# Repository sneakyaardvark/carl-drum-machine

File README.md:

# C.A.R.L. — Clocked Asynchronous Rhythm Logician

**Team 05:**  
Bao Nguyen  
Andrew Stanton  
Christian Mickelson  
Ethan Budde  

---

## Overview
C.A.R.L. is a portable drum sequencer that lets users tap out, save, and play rhythmic patterns. It operates independently with onboard controls, display, and speaker.

---

## Features
- Sequences and plays drum beats  
- Onboard speaker and volume control  
- Standalone operation (no computer required)  
- 13 pushbuttons, LED indicators, LCD display  
- Optional MIDI, SD card, and battery power  

---

## Hardware
- **Processor:** ESP32  
- **Display:** 20×4 LCD  
- **Inputs:** 13 pushbuttons, 4 potentiometers  
- **Outputs:** LEDs, speaker (8 Ω), LCD  
- **Power:** 5 V barrel jack or optional battery  
- **Enclosure:** Laser-cut plywood + 3D printed parts  

---

## Development
- **Electronics:** KiCAD  
- **3D Design:** Fusion 360  
- **Firmware:** Arduino / PlatformIO

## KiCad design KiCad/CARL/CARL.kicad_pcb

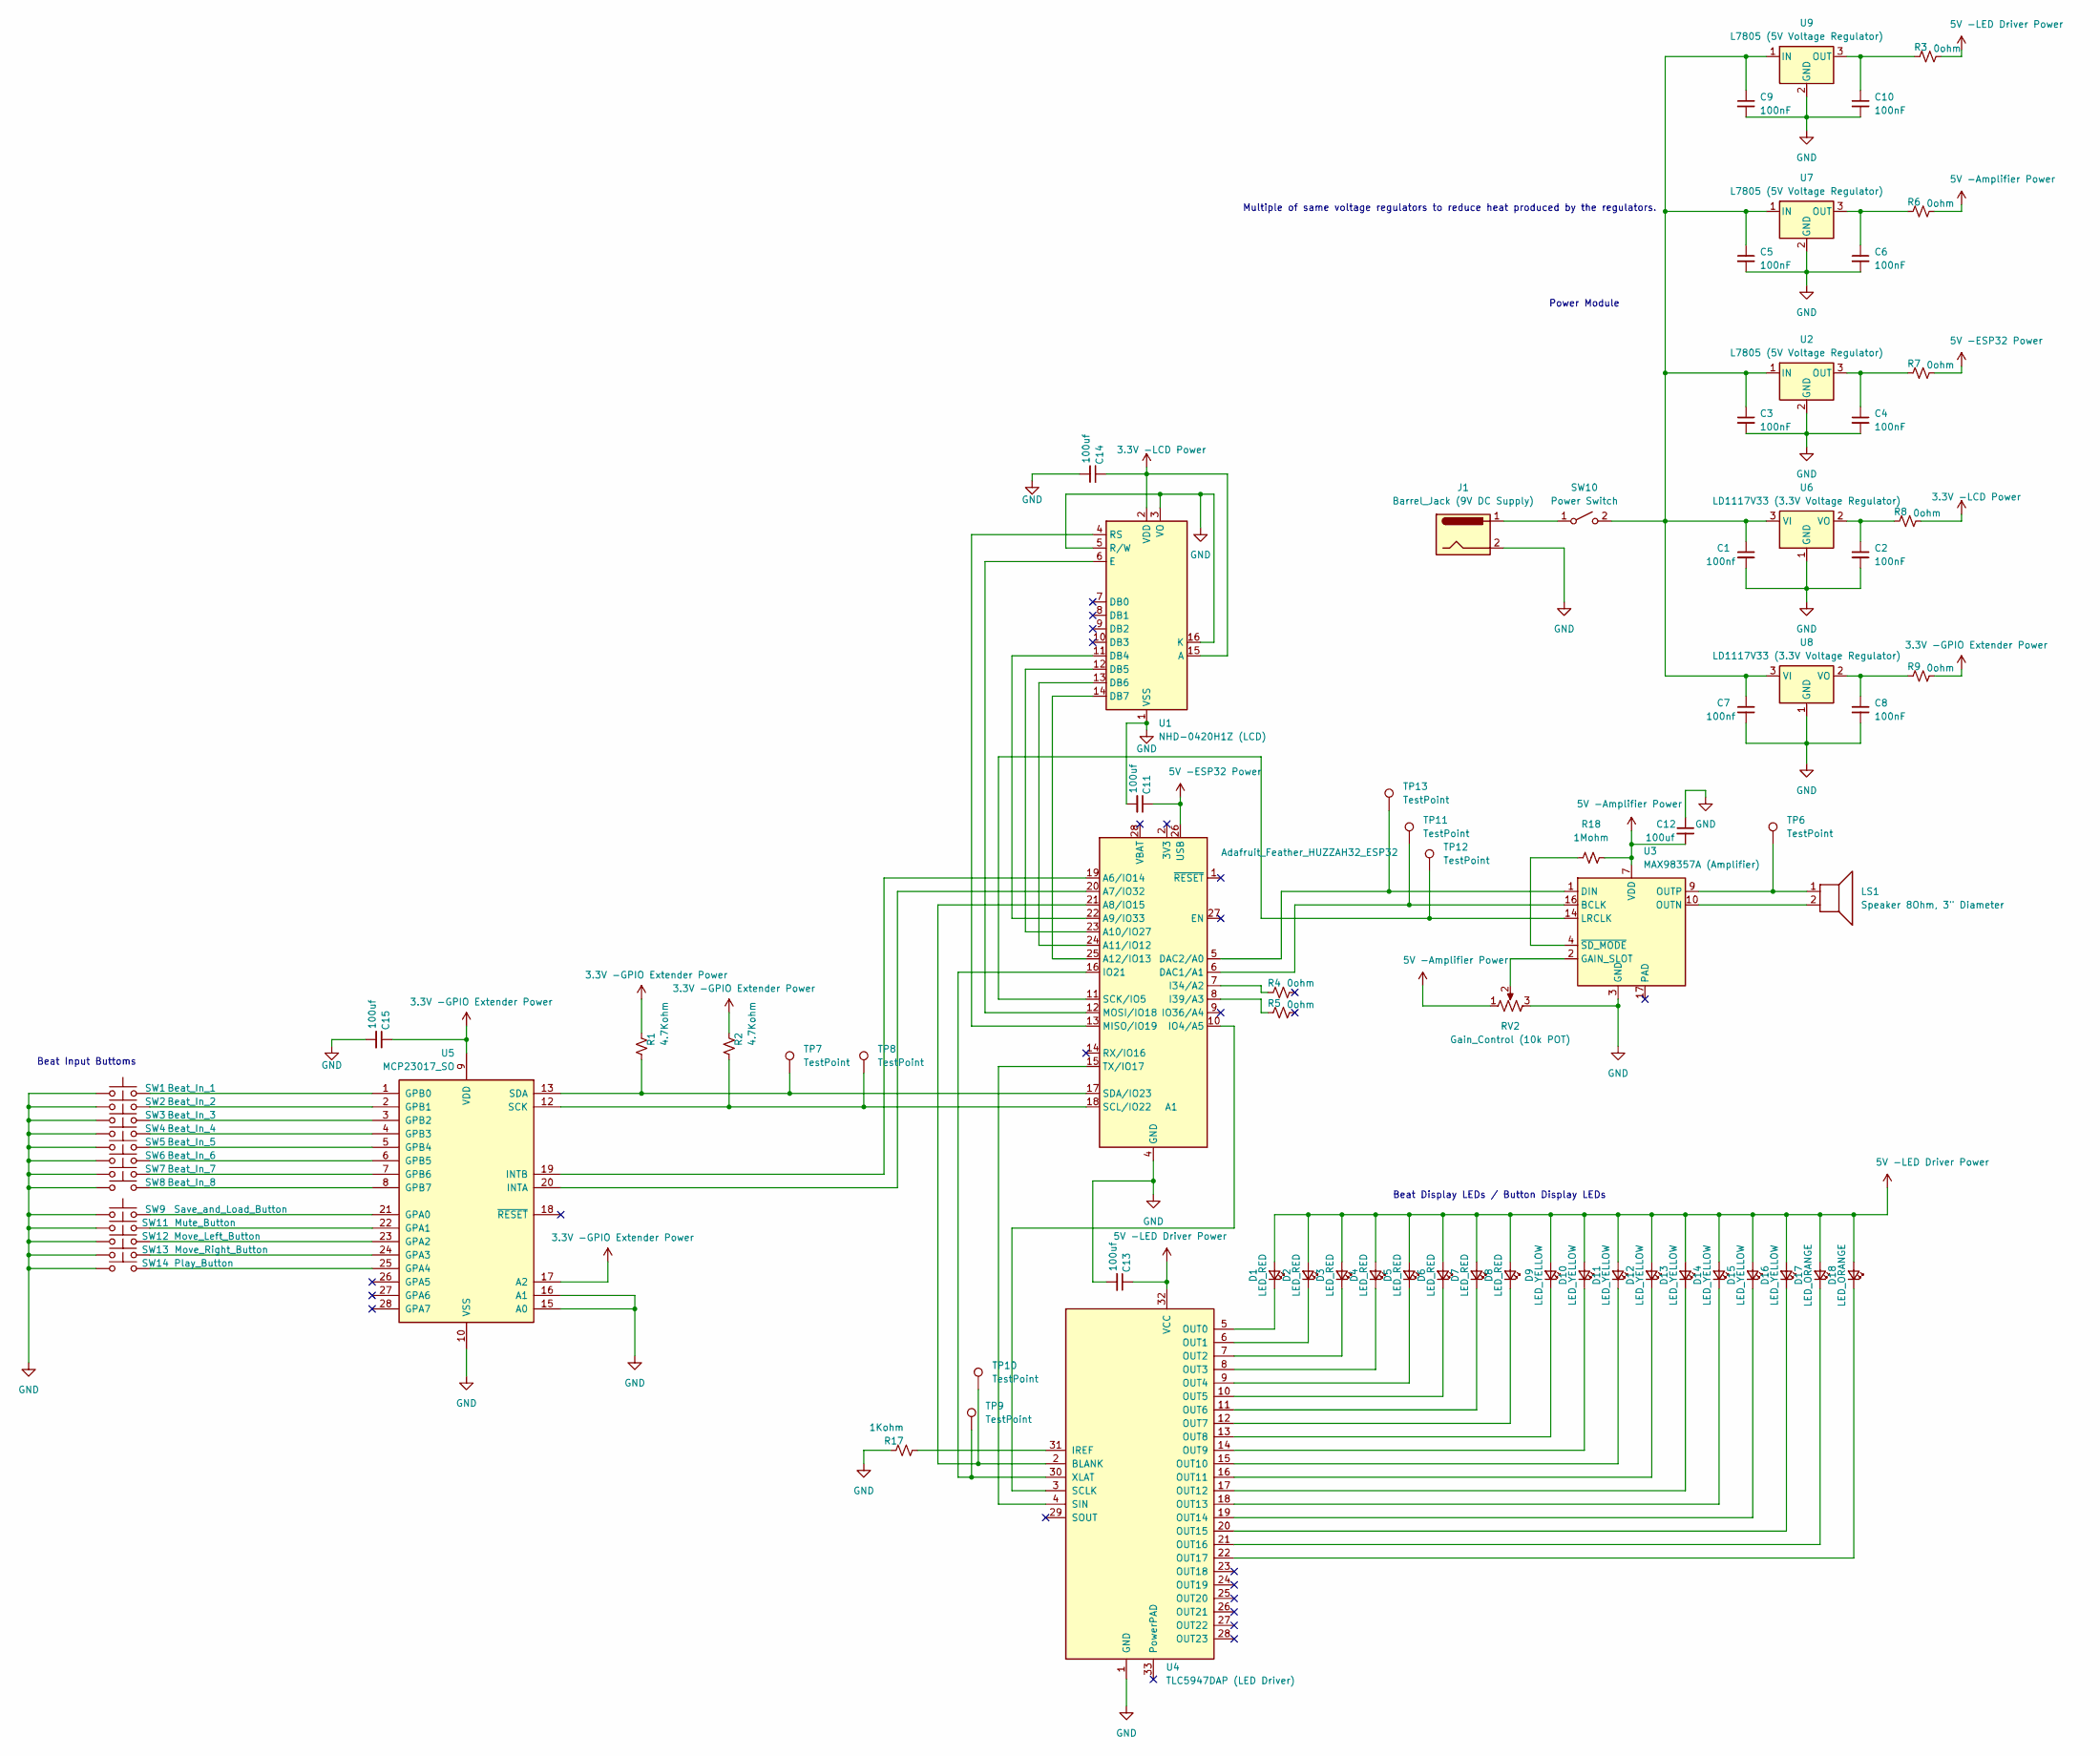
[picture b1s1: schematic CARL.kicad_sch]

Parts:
A1: Adafruit_Feather_HUZZAH32_ESP32; Adafruit_Feather
C1, C7: 100nf; C_0805_2012Metric
C2, C3, C4, C5, C6, C8, C9, C10: 100nF; C_0805_2012Metric
C11, C12, C13, C14, C15: 100uf; C_0805_2012Metric
D1, D2, D3, D4, D5, D6, D7, D8: LED_RED; LED_D5.0mm
D9, D10, D11, D12, D13, D14, D15, D16: LED_YELLOW; LED_D5.0mm
D17, D18: LED_ORANGE; LED_D5.0mm
J1: Barrel_Jack (9V DC Supply); BarrelJack_CUI_PJ-036AH-SMT_Horizontal
LS1: Speaker 8Ohm, 3" Diameter; Speaker_CUI_CMR-1206S-67
R1, R2: 4.7Kohm; R_0805_2012Metric
R3, R4, R5, R6, R7, R8, R9: 0ohm; PinHeader_1x02_P2.54mm_Vertical
R17: 1Kohm; R_0805_2012Metric
R18: 1Mohm; R_0805_2012Metric
RV2: Gain_Control (10k POT); Potentiometer_ACP_CA6-VSMD_Vertical
SW1: Beat_In_1; SW_Cherry_MX_1.00u_PCB
SW2: Beat_In_2; SW_Cherry_MX_1.00u_PCB
SW3: Beat_In_3; SW_Cherry_MX_1.00u_PCB
SW4: Beat_In_4; SW_Cherry_MX_1.00u_PCB
SW5: Beat_In_5; SW_Cherry_MX_1.00u_PCB
SW6: Beat_In_6; SW_Cherry_MX_1.00u_PCB
SW7: Beat_In_7; SW_Cherry_MX_1.00u_PCB
SW8: Beat_In_8; SW_Cherry_MX_1.00u_PCB
SW9: Save_and_Load_Button; SW_Cherry_MX_1.00u_PCB
SW10: Power Switch; SW_DIP_SPSTx01_Slide_6.7x4.1mm_W6.73mm_P2.54mm_LowProfile_J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
SW11: Mute_Button; SW_Cherry_MX_1.00u_PCB
SW12: Move_Left_Button; SW_Cherry_MX_1.00u_PCB
SW13: Move_Right_Button; SW_Cherry_MX_1.00u_PCB
SW14: Play_Button; SW_Cherry_MX_1.00u_PCB
TP6, TP7, TP8, TP9, TP10, TP11, TP12, TP13: TestPoint; PinHeader_1x01_P2.54mm_Vertical
U1: NHD-0420H1Z (LCD); NHD-0420H1Z
U2, U7, U9: L7805 (5V Voltage Regulator); TO-220-3_Vertical
U3: MAX98357A (Amplifier); TQFN-16-1EP_3x3mm_P0.5mm_EP1.23x1.23mm
U4: TLC5947DAP (LED Driver); HTSSOP-32-1EP_6.1x11mm_P0.65mm_EP5.2x11mm_Mask4.11x4.36mm_T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
U5: MCP23017_SO; SOIC-28W_7.5x17.9mm_P1.27mm
U6, U8: LD1117V33 (3.3V Voltage Regulator); TO-220-3_Vertical

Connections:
3.3V -GPIO Extender Power: C15.1, R1.1, R2.1, R9.2, U5.9 (VDD), U5.17 (A2)
3.3V -LCD Power: C14.1, R8.2, U1.2 (VDD), U1.15 (A); also elsewhere on the board
5V -Amplifier Power: C12.2, R6.2, R18.2, RV2.1, U3.7 (VDD), U3.8 (VDD)
5V -ESP32 Power: A1.26 (USB), C11.1, R7.2
5V -LED Driver Power: C13.1, D1.2 (A), D2.2 (A), D3.2 (A), D4.2 (A), D5.2 (A), D6.2 (A), D7.2 (A), D8.2 (A), D9.2 (A), D10.2 (A), D11.2 (A), D12.2 (A), D13.2 (A), D14.2 (A), D15.2 (A), D16.2 (A), D17.2 (A), D18.2 (A), R3.2, U4.32 (VCC)
GND: A1.4 (GND), C1.2, C2.2, C3.2, C4.2, C5.2, C6.2, C7.2, C8.2, C9.2, C10.2, C11.2, C12.1, C13.2, C14.2, C15.2, J1.2, R17.1, RV2.3, SW1.1, SW2.1, SW3.1, SW4.1, SW5.1, SW6.1, SW7.1, SW8.1, SW9.1, SW11.1, SW12.1, SW13.1, SW14.1, U1.1 (VSS), U1.3 (VO), U1.5 (R/W), U1.16 (K), U2.2 (GND), U3.3 (GND), U3.11 (GND), U3.15 (GND), U4.1 (GND), U5.10 (VSS), U5.15 (A0), U5.16 (A1), U6.1 (GND), U7.2 (GND), U8.1 (GND), U9.2 (GND)
unnamed: A1.19 (A6/IO14), U5.19 (INTB)
unnamed: A1.20 (A7/IO32), U5.20 (INTA)
unnamed: A1.21 (A8/IO15), TP10.1, U4.2 (BLANK)
unnamed: A1.22 (A9/IO33), U1.11 (DB4)
unnamed: A1.23 (A10/IO27), U1.12 (DB5)
unnamed: A1.24 (A11/IO12), U1.13 (DB6)
unnamed: A1.25 (A12/IO13), U1.14 (DB7)
unnamed: A1.6 (DAC1/A1), TP11.1, U3.16 (BCLK)
unnamed: A1.5 (DAC2/A0), TP13.1, U3.1 (DIN)
unnamed: A1.7 (I34/A2), R4.1
unnamed: A1.8 (I39/A3), R5.1
unnamed: A1.10 (IO4/A5), U4.3 (SCLK)
unnamed: A1.16 (IO21), TP9.1, U4.30 (XLAT)
unnamed: A1.13 (MISO/IO19), U1.4 (RS)
unnamed: A1.12 (MOSI/IO18), U1.6 (E)
unnamed: A1.11 (SCK/IO5), TP12.1, U3.14 (LRCLK)
unnamed: A1.18 (SCL/IO22), R2.2, TP8.1, U5.12 (SCK)
unnamed: A1.17 (SDA/IO23), R1.2, TP7.1, U5.13 (SDA)
unnamed: A1.15 (TX/IO17), U4.4 (SIN)
unnamed: D1.1 (K), U4.5 (OUT0)
unnamed: D2.1 (K), U4.6 (OUT1)
unnamed: D3.1 (K), U4.7 (OUT2)
unnamed: D4.1 (K), U4.8 (OUT3)
unnamed: D5.1 (K), U4.9 (OUT4)
unnamed: D6.1 (K), U4.10 (OUT5)
unnamed: D7.1 (K), U4.11 (OUT6)
unnamed: D8.1 (K), U4.12 (OUT7)
unnamed: D9.1 (K), U4.13 (OUT8)
unnamed: D10.1 (K), U4.14 (OUT9)
unnamed: D11.1 (K), U4.15 (OUT10)
unnamed: D12.1 (K), U4.16 (OUT11)
unnamed: D13.1 (K), U4.17 (OUT12)
unnamed: D14.1 (K), U4.18 (OUT13)
unnamed: D15.1 (K), U4.19 (OUT14)
unnamed: D16.1 (K), U4.20 (OUT15)
unnamed: D17.1 (K), U4.21 (OUT16)
unnamed: D18.1 (K), U4.22 (OUT17)
unnamed: J1.1, SW10.1 (A)
unnamed: C1.1, C3.1, C5.1, C7.1, C9.1, SW10.2 (B), U2.1 (IN), U6.3 (VI), U7.1 (IN), U8.3 (VI), U9.1 (IN)
unnamed: C4.1, R7.1, U2.3 (OUT)
unnamed: RV2.2, U3.2 (GAIN_SLOT)
unnamed: LS1.2, U3.10 (OUTN)
unnamed: LS1.1, TP6.1, U3.9 (OUTP)
unnamed: R18.1, U3.4 (~SD_MODE)
unnamed: R17.2, U4.31 (IREF)
unnamed: SW9.2, U5.21 (GPA0)
unnamed: SW11.2, U5.22 (GPA1)
unnamed: SW12.2, U5.23 (GPA2)
unnamed: SW13.2, U5.24 (GPA3)
unnamed: SW14.2, U5.25 (GPA4)
unnamed: SW1.2, U5.1 (GPB0)
unnamed: SW2.2, U5.2 (GPB1)
unnamed: SW3.2, U5.3 (GPB2)
unnamed: SW4.2, U5.4 (GPB3)
unnamed: SW5.2, U5.5 (GPB4)
unnamed: SW6.2, U5.6 (GPB5)
unnamed: SW7.2, U5.7 (GPB6)
unnamed: SW8.2, U5.8 (GPB7)
unnamed: C2.1, R8.1, U6.2 (VO)
unnamed: C6.1, R6.1, U7.3 (OUT)
unnamed: C8.1, R9.1, U8.2 (VO)
unnamed: C10.1, R3.1, U9.3 (OUT)

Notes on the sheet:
Beat Input Buttoms
Multiple of same voltage regulators to reduce heat produced by the regulators.
Power Module
Beat Display LEDs / Button Display LEDs

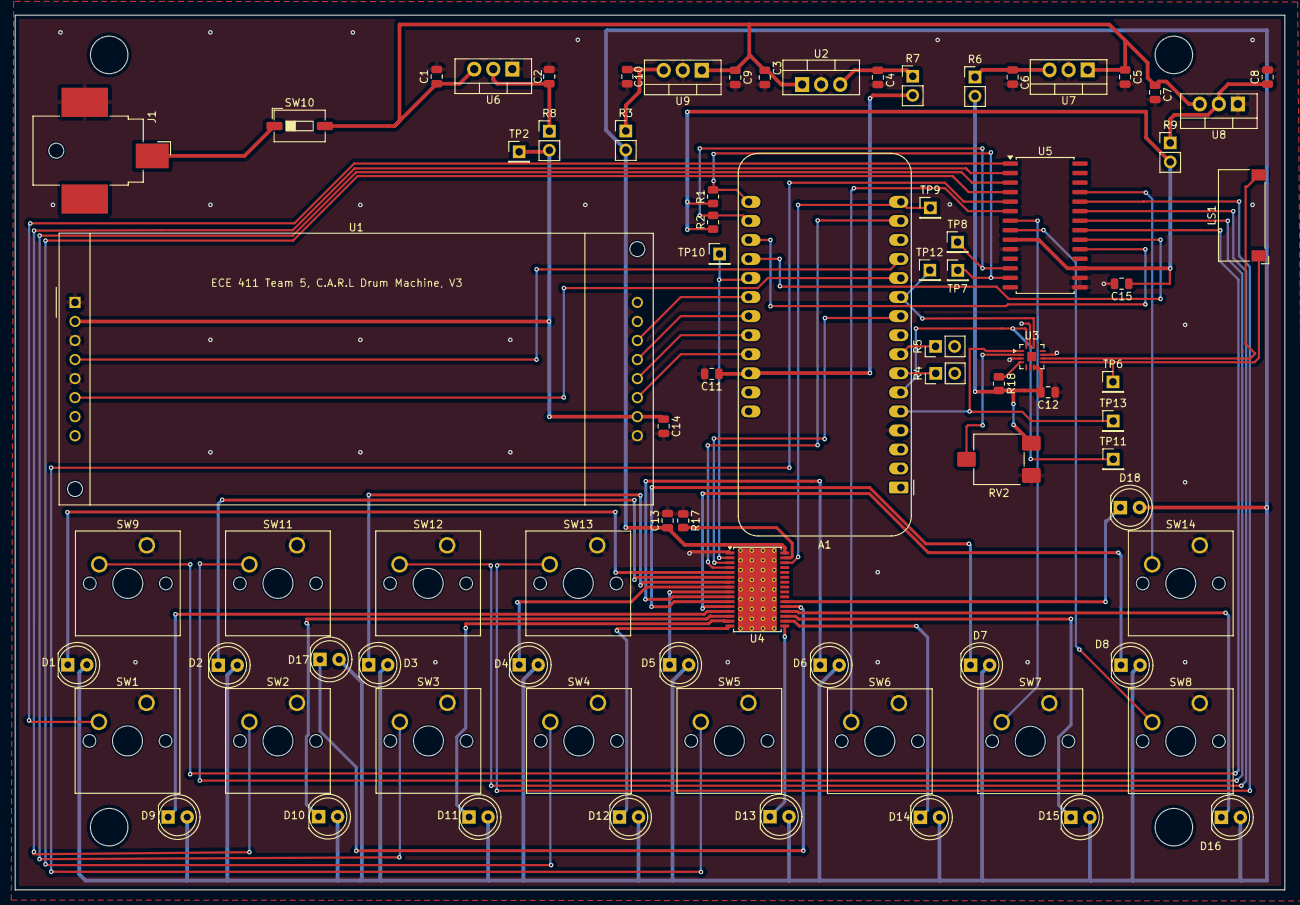
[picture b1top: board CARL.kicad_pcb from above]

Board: 2 copper layers, 169.3 x 116.7 mm, 80 parts (0 on the bottom side), 68 nets.

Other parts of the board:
TP2: TestPoint; PinHeader_1x01_P2.54mm_Vertical

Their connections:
3.3V -LCD Power: TP2.1; also elsewhere on the board

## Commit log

2025-10-23 Add files via upload
    BOM Rev.1
2025-10-23 Create README.md
    Rev.1
2025-10-23 README.md
2025-10-24 feat: flake.nix devshell
2025-10-24 feat: update gitignore for pio
2025-10-24 feat: use platformio
2025-10-24 feat: data types for beat patterns
2025-10-24 revised BOM, reorganized existing file structure for docs
2025-10-28 feat: unit testing
2025-10-28 refactor: rename entrypoint to main.cpp
2025-10-28 fix: use custom beat_pattern type instead of uint32
2025-10-28 refactor: better names for gray code funcs
2025-10-28 style: camelCase func names
2025-10-28 refactor: use uint8_t over byte
2025-10-28 feat: input event abstraction
2025-10-28 feat: use newest arduino-esp32 via pioarduino
2025-10-28 feat: update gitignore for kicad; reformat
2025-10-29 WIP KiCad Schematic
    Work in progress KiCad schematic containing the microcontroller, LCD, and LED driver along with LEDs it drives.
2025-10-30 Update CARL.kicad_sch
    Edited button layout to work correctly and removed resistors so we can instead utilize the ESP32's built in pullup resistor functionality.
2025-10-30 refactor: BeatPattern is now a class
2025-10-30 fix: header path
2025-10-30 refactor: integrate beat pattern as a class into main header
2025-10-30 feat: getter for BeatPattern
2025-10-30 fix: headers
2025-10-30 changed default tempo
2025-10-30 fixed bit movement logic
2025-10-30 comments for logical decomposition
2025-10-31 Preliminary Schematic Revision 2
    Fixed connections to LCD. Edited connections to Amplifier to (hopefully) work. Added GPIO extender and moved all button connections off of the esp32 and onto the extender.
2025-11-06 Schematic Update / Preliminary PCB
    -Added remaining LEDs to the schematic
    -Edited some connections with the amplifier to function correctly (hopefully)
    -Edited connections between LEDs and LED driver to correspond with what the data sheet shows. The LEDs now receive VCC instead of GND and all resistors have been removed from them with a new one adde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
2025-11-06 feat: add ccls to flake
2025-11-06 docs: wk06 status report
2025-11-07 feat(flake): add pio udev rules
2025-11-07 fix: set bits properly rather than ANDing
2025-11-07 fix: remove redundant param in cycleBeat
2025-11-07 test: add tests for BeatPattern cycling
2025-11-11 docs: Doxygen support
2025-11-11 feat: HardwareTest classification
2025-11-13 PCB V2 and Schematic V3
    -Updated schematic to utilize new voltage regulator setup.
    -Updated PCB to reflect changes done in the schematic
2025-11-14 feat: CarlAudio system, very WIP
2025-11-14 fix: make WAV I2S output actually work
2025-11-14 refactor: move wav header type to separate header
2025-11-14 fix: get_sample returns wrong type
2025-11-14 fix: I2S pins
2025-11-14 fix: change method defs to 8 bit WAV depth
2025-11-14 docs: better explanation of sample manipulation
2025-11-14 refactor: WAV header bytes are unsigned
2025-11-14 fix(CarlAudio): incorrect I2S pins
2025-11-14 fix: offset frames address by buffer position
2025-11-14 fix: cleanup commented code
2025-11-14 fix: remove redundant cstdint
2025-11-14 refactor: rename struct member wav to src
2025-11-14 feat: full WAV header and 8 bit depth
2025-11-14 fix: use data types more directly (PCM samples are signed), change func params where needed
2025-11-14 test: add i2s tests
2025-11-14 feat: use SPIFFS as default pio filesystem
2025-11-14 test(CarlAudio): add tests for loading WAV from SPIFFS
2025-11-14 feat: test wav sine.wav
2025-11-14 fix: ++ operator deprecated for volatile
2025-11-14 docs(CarlAudio): doc comments
2025-11-17 fix: full 16 bit output on I2S working!
2025-11-18 Minor Schematic Update
2025-11-18 docs: add pcb review notes
2025-11-19 Merge branch 'sample-streaming'
    Squashed commit of the following:
    commit e3bee00b376309e504e5cf92ba370c6b4a4fad70
    Author: Sneaky Aardvark <81195290+sneakyaardvark@users.noreply.github.com>
    Date: Tue Nov 18 16:18:13 2025 -0800
    test: add test for i2s streaming
    commit 19241e77e7c422783674baf48b3c57fb1aa4e470
2025-11-19 feat: add uClock library
2025-11-19 refactor: beat pattern improvements
2025-11-19 docs: add doc comments to BeatPattern
2025-11-19 wip 2
2025-11-19 syntax: c++ class namespace
2025-11-20 Final Schematic and PCB
    -Added test points and 0 ohm resistors to the schematic.
    -Added pullup resistors to I2C line
    -Updated PCB and redid layout according to updated schematic.
    -LED footprint updated to typical through hole PCB.
    -Generated Gerbur Files
    -Added Mounting Holes and Silkscreen
2025-11-20 feat - i2c library
2025-11-21 feat - carl i2c library
2025-11-21 wip - serial library
2025-11-21 wip - debugMode
2025-11-21 etc - emergency testing (dilapidated)
2025-11-25 feat - i2c library v1.0
2025-11-25 feat - modeDebug lib 0.1
2025-11-25 feat - carlSerial lib wip
2025-11-25 wip - main bruteforce testing
2025-11-25 feat: playback WIP
2025-11-26 playback wip
2025-11-26 rev - clerical
2025-11-26 rev - serial lib v0.2
2025-11-26 test - more hardcoding testing wip
2025-12-02 increase number of I2S frames sent per I2S tick
2025-12-02 test: add test file for playback
2025-12-03 Create 3D Models
2025-12-11 docs: label I2S pinouts with physicals pins
2025-12-11 refactor: simpler beatpattern impl
2025-12-11 refactor: remove callback friend
2025-12-11 test: update streaming test
2025-12-11 docs: test plan
2025-12-11 feat: header-only input events
2025-12-11 serial/i2c library updates
2025-12-11 wip testing funcs
2025-12-11 some prints
2025-12-11 work patch
2025-12-11 builds but does not work
    need to change pinouts
2025-12-11 refactor: better mutex usage
2025-12-11 Add files via upload
    All printed mechanical parts for the enclosure.
2025-12-11 Delete 3D Models
    Duplicate
2025-12-11 Load in 3D Models
2025-12-12 docs: add PDS (it was missing?)
2025-12-12 docs: add project schedule
2025-12-12 feat: playback from main
